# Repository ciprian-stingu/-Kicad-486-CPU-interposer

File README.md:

# Kicad-486-CPU-interposer
**486 Cpu Interposer**  
This interposer can be used to troubleshoot not working motherboards which have Socket3/PGA168 sockets.  
All i486 CPU signals are accesible on board connectors. It **should** be compatible with Intel/AMD 486DX/SX/DX2/DX4.  
On DX/SX and DX2 processors, J1 should be connected to VCC but on DX4 it may not be needed.  
The interposer was tested using an Intel 486DX processor.

## Requirements
[Kicad-486-CPU-socket](https://github.com/ciprian-stingu/Kicad-486-CPU-socket)

## PCB options:
* Material : FR-4, TG130 
* Layers : 2 
* Thickness : 1.0 mm

## Construction
Use round female pin header (1x40 pins, step 2.54mm) to construct the socket, starting from inside to the outside.  
After each row from top, solder to the undeside, pins extracted from round female pin header. Because the thickness of the board is only 1 mm, you will not have any problems soldering them on underside.

## Images

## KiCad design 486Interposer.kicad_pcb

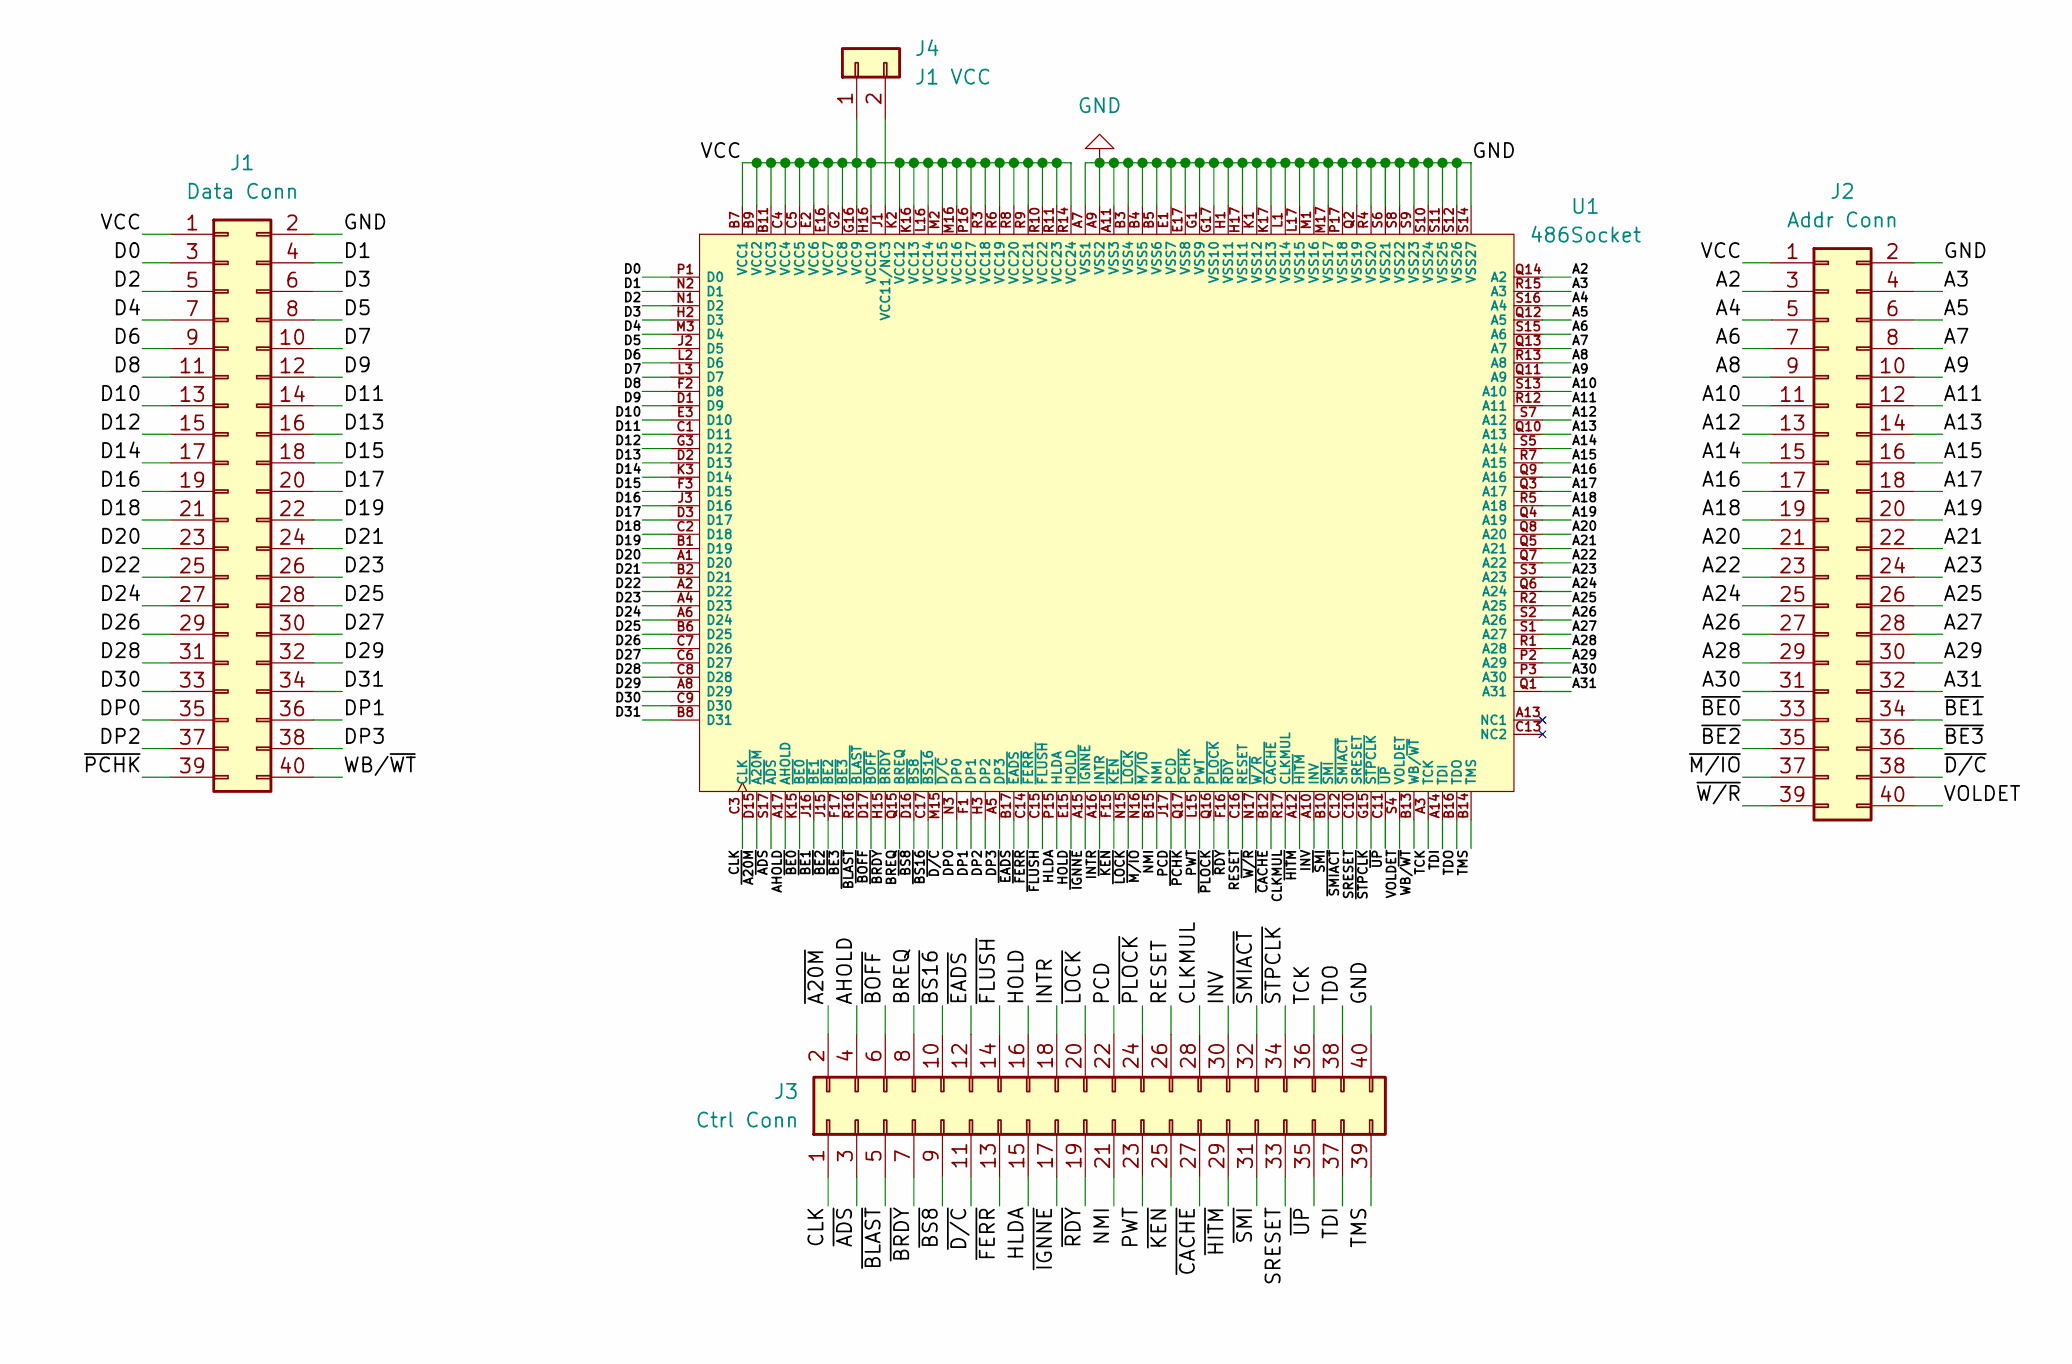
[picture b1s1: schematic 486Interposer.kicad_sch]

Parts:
J1: Data Conn; PinHeader_2x20_P2.54mm_Vertical
J2: Addr Conn; PinHeader_2x20_P2.54mm_Vertical
J3: Ctrl Conn; PinHeader_2x20_P2.54mm_Vertical
J4: J1 VCC; PinHeader_1x02_P2.54mm_Horizontal
U1: 486Socket

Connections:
/A2: J2.3, U1.Q14 (A2)
/A3: J2.4, U1.R15 (A3)
/A4: J2.5, U1.S16 (A4)
/A5: J2.6, U1.Q12 (A5)
/A6: J2.7, U1.S15 (A6)
/A7: J2.8, U1.Q13 (A7)
/A8: J2.9, U1.R13 (A8)
/A9: J2.10, U1.Q11 (A9)
/A10: J2.11, U1.S13 (A10)
/A11: J2.12, U1.R12 (A11)
/A12: J2.13, U1.S7 (A12)
/A13: J2.14, U1.Q10 (A13)
/A14: J2.15, U1.S5 (A14)
/A15: J2.16, U1.R7 (A15)
/A16: J2.17, U1.Q9 (A16)
/A17: J2.18, U1.Q3 (A17)
/A18: J2.19, U1.R5 (A18)
/A19: J2.20, U1.Q4 (A19)
/A20: J2.21, U1.Q8 (A20)
/A21: J2.22, U1.Q5 (A21)
/A22: J2.23, U1.Q7 (A22)
/A23: J2.24, U1.S3 (A23)
/A24: J2.25, U1.Q6 (A24)
/A25: J2.26, U1.R2 (A25)
/A26: J2.27, U1.S2 (A26)
/A27: J2.28, U1.S1 (A27)
/A28: J2.29, U1.R1 (A28)
/A29: J2.30, U1.P2 (A29)
/A30: J2.31, U1.P3 (A30)
/A31: J2.32, U1.Q1 (A31)
/AHOLD: J3.4, U1.A17 (AHOLD)
/BREQ: J3.8, U1.Q15 (BREQ)
/CLK: J3.1, U1.C3 (CLK)
/CLKMUL: J3.28, U1.R17 (CLKMUL)
/D0: J1.3, U1.P1 (D0)
/D1: J1.4, U1.N2 (D1)
/D2: J1.5, U1.N1 (D2)
/D3: J1.6, U1.H2 (D3)
/D4: J1.7, U1.M3 (D4)
/D5: J1.8, U1.J2 (D5)
/D6: J1.9, U1.L2 (D6)
/D7: J1.10, U1.L3 (D7)
/D8: J1.11, U1.F2 (D8)
/D9: J1.12, U1.D1 (D9)
/D10: J1.13, U1.E3 (D10)
/D11: J1.14, U1.C1 (D11)
/D12: J1.15, U1.G3 (D12)
/D13: J1.16, U1.D2 (D13)
/D14: J1.17, U1.K3 (D14)
/D15: J1.18, U1.F3 (D15)
/D16: J1.19, U1.J3 (D16)
/D17: J1.20, U1.D3 (D17)
/D18: J1.21, U1.C2 (D18)
/D19: J1.22, U1.B1 (D19)
/D20: J1.23, U1.A1 (D20)
/D21: J1.24, U1.B2 (D21)
/D22: J1.25, U1.A2 (D22)
/D23: J1.26, U1.A4 (D23)
/D24: J1.27, U1.A6 (D24)
/D25: J1.28, U1.B6 (D25)
/D26: J1.29, U1.C7 (D26)
/D27: J1.30, U1.C6 (D27)
/D28: J1.31, U1.C8 (D28)
/D29: J1.32, U1.A8 (D29)
/D30: J1.33, U1.C9 (D30)
/D31: J1.34, U1.B8 (D31)
/DP0: J1.35, U1.N3 (DP0)
/DP1: J1.36, U1.F1 (DP1)
/DP2: J1.37, U1.H3 (DP2)
/DP3: J1.38, U1.A5 (DP3)
/HLDA: J3.15, U1.P15 (HLDA)
/HOLD: J3.16, U1.E15 (HOLD)
/INTR: J3.18, U1.A16 (INTR)
/INV: J3.30, U1.A10 (INV)
/NMI: J3.21, U1.B15 (NMI)
/PCD: J3.22, U1.J17 (PCD)
/PWT: J3.23, U1.L15 (PWT)
/RESET: J3.26, U1.C16 (RESET)
/SRESET: J3.33, U1.C10 (SRESET)
/TCK: J3.36, U1.A3 (TCK)
/TDI: J3.37, U1.A14 (TDI)
/TDO: J3.38, U1.B16 (TDO)
/TMS: J3.39, U1.B14 (TMS)
/VCC: J1.1, J2.1, J4.1, U1.B7 (VCC1), U1.B9 (VCC2), U1.B11 (VCC3), U1.C4 (VCC4), U1.C5 (VCC5), U1.E2 (VCC6), U1.E16 (VCC7), U1.G2 (VCC8), U1.G16 (VCC9), U1.H16 (VCC10), U1.K2 (VCC12), U1.K16 (VCC13), U1.L16 (VCC14), U1.M2 (VCC15), U1.M16 (VCC16), U1.P16 (VCC17), U1.R3 (VCC18), U1.R6 (VCC19), U1.R8 (VCC20), U1.R9 (VCC21), U1.R10 (VCC22), U1.R11 (VCC23), U1.R14 (VCC24)
/VOLDET: J2.40, U1.S4 (VOLDET)
/WB/~WT: J1.40, U1.B13 (WB/~WT)
/~A20M: J3.2, U1.D15 (~A20M)
/~ADS: J3.3, U1.S17 (~ADS)
/~BE0: J2.33, U1.K15 (~BE0)
/~BE1: J2.34, U1.J16 (~BE1)
/~BE2: J2.35, U1.J15 (~BE2)
/~BE3: J2.36, U1.F17 (~BE3)
/~BLAST: J3.5, U1.R16 (~BLAST)
/~BOFF: J3.6, U1.D17 (~BOFF)
/~BRDY: J3.7, U1.H15 (~BRDY)
/~BS8: J3.9, U1.D16 (~BS8)
/~BS16: J3.10, U1.C17 (~BS16)
/~CACHE: J3.27, U1.B12 (~CACHE)
/~D/C: J2.38, J3.11, U1.M15 (~D/C)
/~EADS: J3.12, U1.B17 (~EADS)
/~FERR: J3.13, U1.C14 (~FERR)
/~FLUSH: J3.14, U1.C15 (~FLUSH)
/~HITM: J3.29, U1.A12 (~HITM)
/~IGNNE: J3.17, U1.A15 (~IGNNE)
/~KEN: J3.25, U1.F15 (~KEN)
/~LOCK: J3.20, U1.N15 (~LOCK)
/~M/IO: J2.37, U1.N16 (~M/IO)
/~PCHK: J1.39, U1.Q17 (~PCHK)
/~PLOCK: J3.24, U1.Q16 (~PLOCK)
/~RDY: J3.19, U1.F16 (~RDY)
/~SMIACT: J3.32, U1.C12 (~SMIACT)
/~SMI: J3.31, U1.B10 (~SMI)
/~STPCLK: J3.34, U1.G15 (~STPCLK)
/~UP: J3.35, U1.C11 (~UP)
/~W/R: J2.39, U1.N17 (~W/R)
GND: J1.2, J2.2, J3.40, U1.A7 (VSS1), U1.A9 (VSS2), U1.A11 (VSS3), U1.B3 (VSS4), U1.B4 (VSS5), U1.B5 (VSS6), U1.E1 (VSS7), U1.E17 (VSS8), U1.G1 (VSS9), U1.G17 (VSS10), U1.H1 (VSS11), U1.H17 (VSS11), U1.K1 (VSS12), U1.K17 (VSS13), U1.L1 (VSS14), U1.L17 (VSS15), U1.M1 (VSS16), U1.M17 (VSS17), U1.P17 (VSS18), U1.Q2 (VSS19), U1.R4 (VSS20), U1.S6 (VSS21), U1.S8 (VSS22), U1.S9 (VSS23), U1.S10 (VSS24), U1.S11 (VSS25), U1.S12 (VSS26), U1.S14 (VSS27)
unnamed: J4.2, U1.J1 (VCC11/NC3)

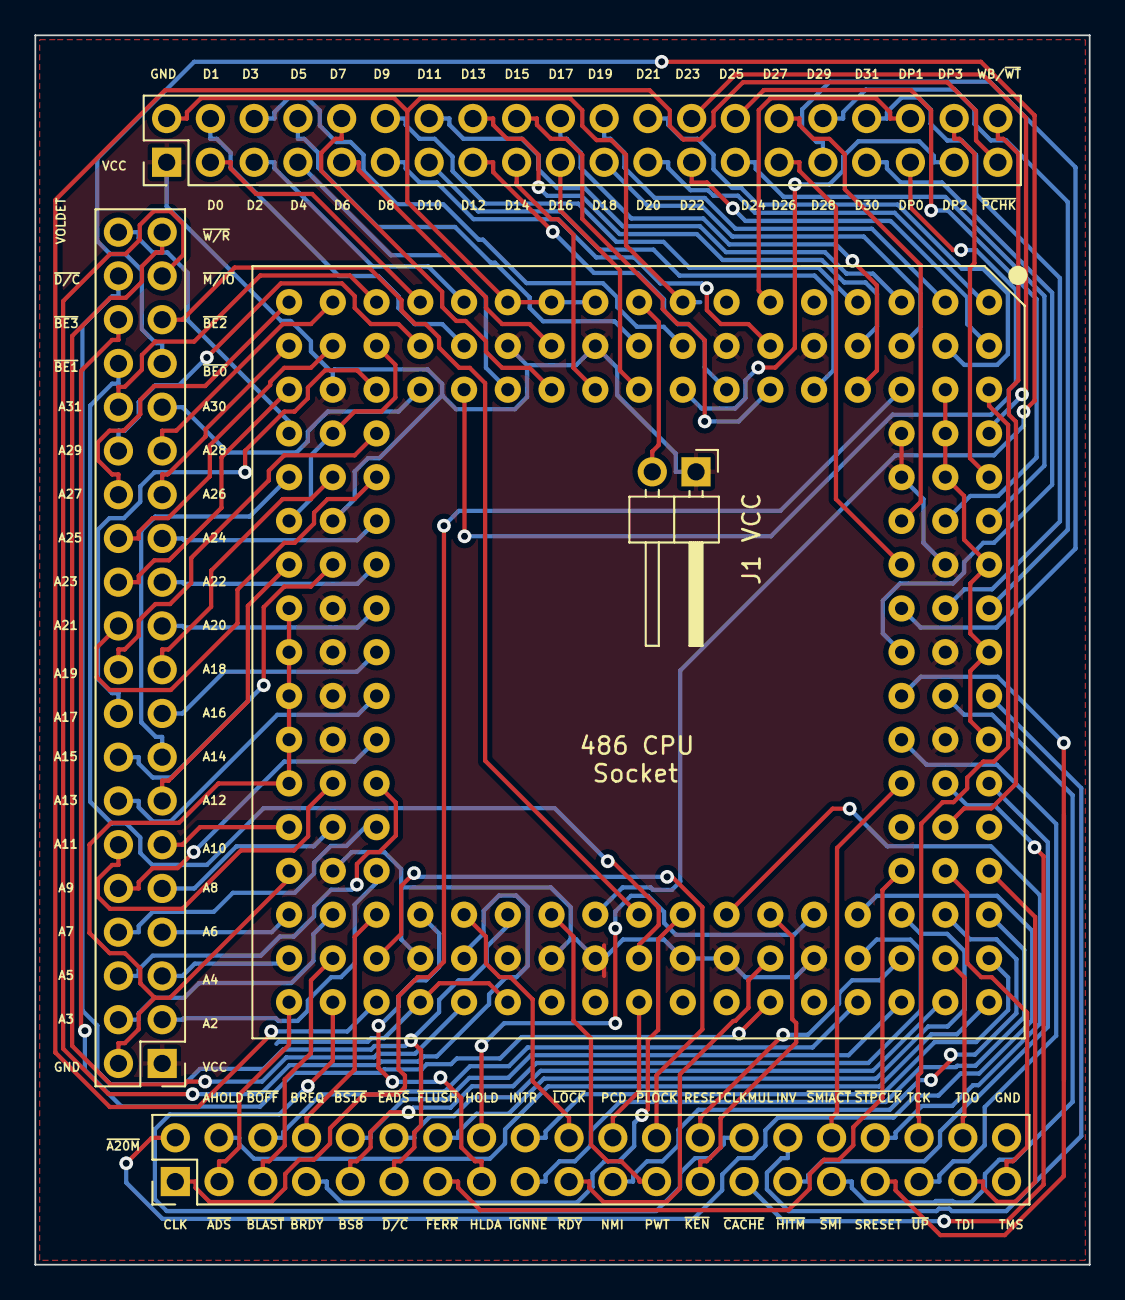
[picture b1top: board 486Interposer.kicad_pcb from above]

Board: 2 copper layers, 61.2 x 71.4 mm, 5 parts (0 on the bottom side), 117 nets.

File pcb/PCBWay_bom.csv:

designator,quantity,value,pack,mpn,mount_type
J1,1,Data Conn,PinHeader_2x20_P2.54mm_Vertical,,tht
J2,1,Addr Conn,PinHeader_2x20_P2.54mm_Vertical,,tht
J3,1,Ctrl Conn,PinHeader_2x20_P2.54mm_Vertical,,tht
J4,1,J1 VCC,PinHeader_1x02_P2.54mm_Horizontal,,tht
U1,1,486Socket,486Socket,,tht

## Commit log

2024-03-06 Fix readme typo
